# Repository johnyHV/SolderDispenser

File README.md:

# Solder paste dispenser

# Change Log

### Version 1.1 [HW v1.1, SW v1.1]
- pridana funkcia auto pull efektu. Toznamena, ze po pusteni PUSH tlacidla sa krokovy motor otoci o X krokov spat, vdaka comu prestane tlacit na spajkovaciu pastu. Efekt mozete zapnut pomocou definicie **M_A_PULL_E** v subore **MCU_cfg.h**.  Definiciou **M_A_PULL_ST** nastavujete pocet krokov o kolko sa krokov motor vrati spet. Tuto hodnotu je potrebne odladit pre kazdeho uzivatela, no myslim ze 100 krokov bude dost. Definiciou **M_A_PULL_SP** nastavite rychlost otacania krokoveho motora, pri otacani.
- pridany vypis SW verzie do konzoly
- aktualizovana doxygen dokumentacia

### Version 1.2 [HW v1.1, SW v1.2]
- pridana moznost zapnutia/vypnutia auto pull modu pomocou tlacidiel.  Defaultne je auto pull mod vypnuty, pomocou definicie **M_A_PULL_E**. Pre zapnutie je potrebne podrzat 5 sekund tlacidlo **MODE**. Po 5 sekundach zsvieti led **STATUS** na 1 sekundu. Vtedy je potrebne pustit tlacidlo **MODE**. Touto sekvenciou bol zapnuty auto pull mod. Ak ho chcete vypnut, znova je potrebne podrzat 5 sekund tlacidlo  **MODE**. Volba zapnutia/vypnutia auto pull modu sa neuklada do EEPROM pamete, cize po kazdom restarte je nastavena na hodnotu v definicii **M_A_PULL_E**.
- aktualizacia doxygen dokumentacie

### Version 1.3 [HW v1.2, SW v1.2]
- pridany kondenzator 1uF k napajaniu MCU

### Version 1.4 [HW v1.3, SW v1.2]
- pridany kondenzator 100nF k CH340 na 3,3V vystup.

# Bug

### Bug 0001
**Opis chyby:** 
chyba v HW zapojeni pre HW verzie 1.0, 1.1, 1.2. Chybajuci kondenzator 100nF pre CH340 na pine 4, proti zemi.

**Spravanie chyby:**
- OS moze mat problem pri detegcii zariadenia, v pripade pouzitia dlheho USB kabla. Pri dlzke kabla do 20cm bude zariadenie fungovat korektne.
- Moze vzniknut problem pri programovani MCU, kedy OS vypise hlasku nedetegovaneho USB zariadenia.
- Nahodne restarty MCU pocas pouzivania podavaca

**Riesenie:**
- potrebne prispajkovat kondenzator 100nF na pin 4 integrovaneho obvodu CH340 proti zemi. Tak ako je to zobrazene na fotografii

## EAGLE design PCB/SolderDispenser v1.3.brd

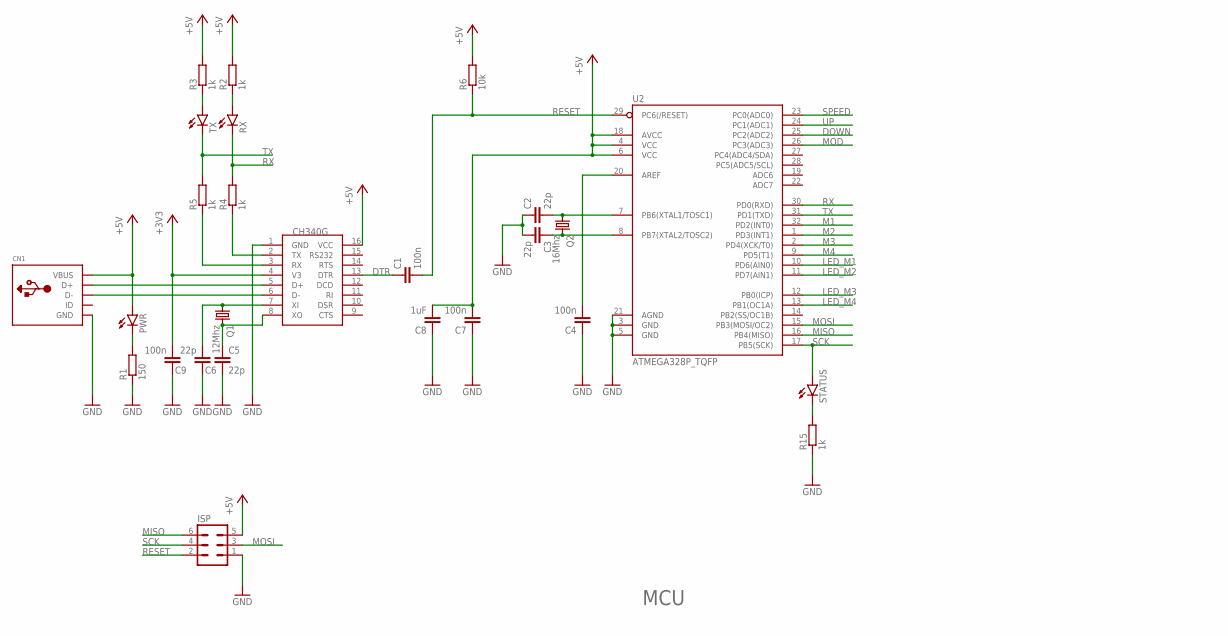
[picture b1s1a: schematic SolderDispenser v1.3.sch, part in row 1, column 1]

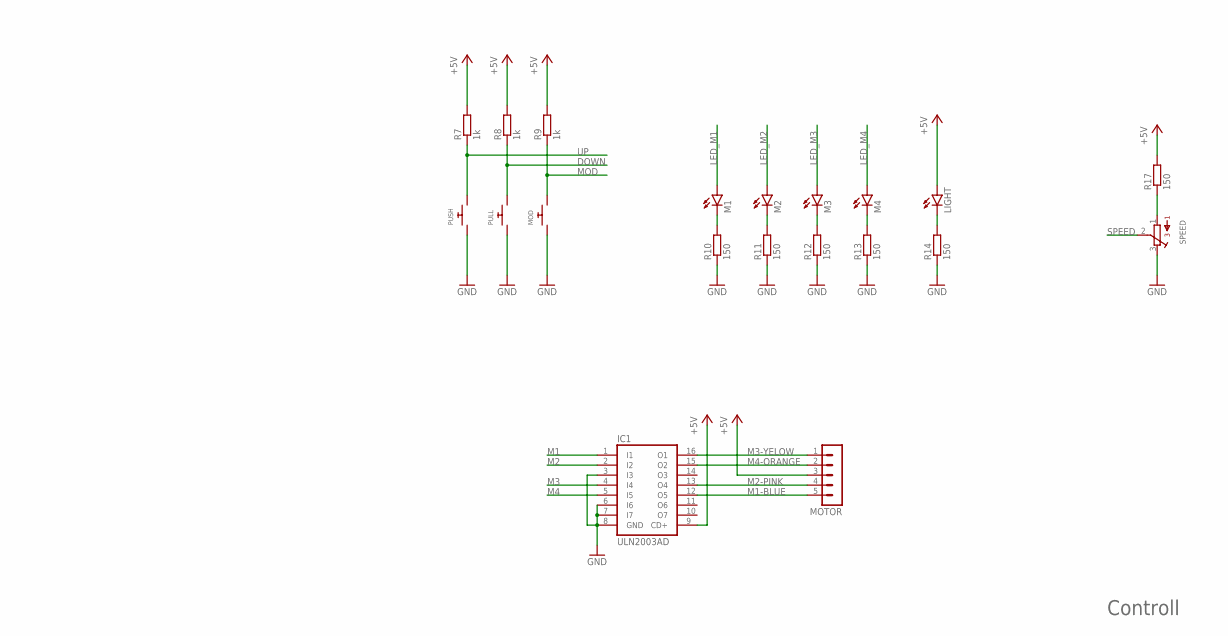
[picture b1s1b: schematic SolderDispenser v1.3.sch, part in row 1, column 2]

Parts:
C1, C4, C7, C9: 100n; C0805
C2, C3, C5, C6: 22p; C0805
C8: 1uF; C0805
CN1: USBMOLEX; USB-MINIB-THM-MOLEX
IC1: ULN2003AD; SO16
ISP: MA03-2
LIGHT: LED5MM
M1, M2, M3, M4: LEDSML0805; SML0805
MOD: SWITCH_PUSHBUTTONEVQ-PE; TACT_PANA-EVQ
MOTOR: MA05-1
PULL: SWITCH_PUSHBUTTONEVQ-PE; TACT_PANA-EVQ
PUSH: SWITCH_PUSHBUTTONEVQ-PE; TACT_PANA-EVQ
PWR: LEDSML0805; SML0805
Q1: 12Mhz; HC49UP
Q2: 16Mhz; HC49UP
R1, R10, R11, R12, R13, R14, R17: 150; R0805
R2, R3, R4, R5, R7, R8, R9, R15: 1k; R0805
R6: 10k; R0805
RX: LEDSML0805; SML0805
SPEED: 3362P
STATUS: LEDSML0805; SML0805
TX: LEDSML0805; SML0805
U2: ATMEGA328P_TQFP; TQFP32-08
U$1: CH340G; SOIC16

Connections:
+3V3: C9.2, U$1.4 (V3)
+5V: C7.2, C8.2, CN1.VBUS, IC1.9 (CD+), ISP.5, LIGHT.A, MOTOR.3, PWR.A, R2.2, R3.2, R6.2, R7.2, R8.2, R9.2, R17.2, U2.4 (VCC), U2.6 (VCC), U2.18 (AVCC), U$1.16 (VCC)
DOWN: PULL.P$2, R8.1, U2.25 (PC2(ADC2))
DTR: C1.1, U$1.13 (DTR)
GND: C2.1, C3.2, C4.1, C5.2, C6.1, C7.1, C8.1, C9.1, CN1.GND, IC1.3 (I3), IC1.6 (I6), IC1.7 (I7), IC1.8 (GND), ISP.1, MOD.P$1, PULL.P$1, PUSH.P$1, R1.1, R10.1, R11.1, R12.1, R13.1, R14.1, R15.1, SPEED.3, U2.3 (GND), U2.5 (GND), U2.21 (AGND), U$1.1 (GND)
LED_M1: M1.A, U2.10 (PD6(AIN0))
LED_M2: M2.A, U2.11 (PD7(AIN1))
LED_M3: M3.A, U2.12 (PB0(ICP))
LED_M4: M4.A, U2.13 (PB1(OC1A))
M1: IC1.1 (I1), U2.32 (PD2(INT0))
M1-BLUE: IC1.12 (O5), MOTOR.5
M2: IC1.2 (I2), U2.1 (PD3(INT1))
M2-PINK: IC1.13 (O4), MOTOR.4
M3: IC1.4 (I4), U2.2 (PD4(XCK/T0))
M3-YELOW: IC1.16 (O1), MOTOR.1
M4: IC1.5 (I5), U2.9 (PD5(T1))
M4-ORANGE: IC1.15 (O2), MOTOR.2
MISO: ISP.6, U2.16 (PB4(MISO))
MOD: MOD.P$2, R9.1, U2.26 (PC3(ADC3))
MOSI: ISP.3, U2.15 (PB3(MOSI/OC2))
unnamed: CN1.D+, U$1.5 (D+)
unnamed: PWR.C, R1.2
unnamed: CN1.D-, U$1.6 (D-)
unnamed: R5.1, U$1.3 (RX)
unnamed: R4.1, U$1.2 (TX)
unnamed: C2.2, Q2.1, U2.7 (PB6(XTAL1/TOSC1))
unnamed: C6.2, Q1.1, U$1.7 (XI)
unnamed: C5.1, Q1.2, U$1.8 (XO)
unnamed: R2.1, RX.A
unnamed: R3.1, TX.A
unnamed: C3.1, Q2.2, U2.8 (PB7(XTAL2/TOSC2))
unnamed: C4.2, U2.20 (AREF)
unnamed: M1.C, R10.2
unnamed: LIGHT.K (C), R14.2
unnamed: M2.C, R11.2
unnamed: R15.2, STATUS.C
unnamed: M3.C, R12.2
unnamed: M4.C, R13.2
unnamed: R17.1, SPEED.1
RESET: C1.2, ISP.2, R6.1, U2.29 (PC6(/RESET))
RX: R4.2, RX.C, U2.30 (PD0(RXD))
SCK: ISP.4, STATUS.A, U2.17 (PB5(SCK))
SPEED: SPEED.2, U2.23 (PC0(ADC0))
TX: R5.2, TX.C, U2.31 (PD1(TXD))
UP: PUSH.P$2, R7.1, U2.24 (PC1(ADC1))

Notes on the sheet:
MCU
Controll

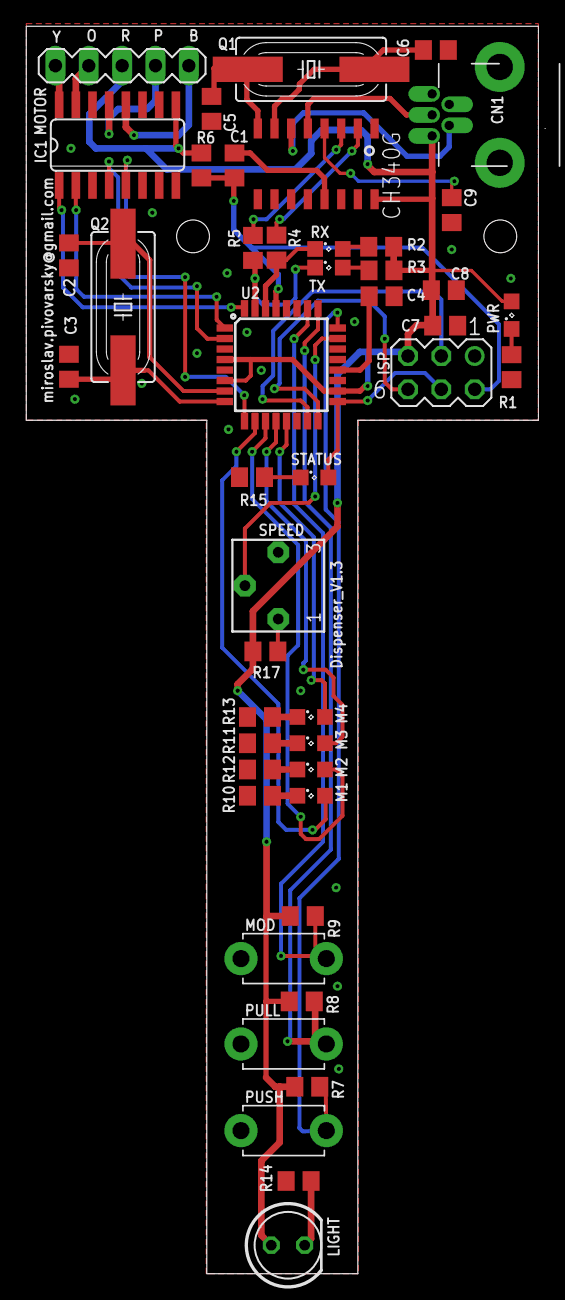
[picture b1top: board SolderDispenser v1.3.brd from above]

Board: 2 copper layers, 39.0 x 95.0 mm, 46 parts (0 on the bottom side), 45 nets.

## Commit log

2020-05-02 - Add source
2020-05-02 [3D]
    - Add 3D model for Syringe 18.6mm
2020-05-02 [Documentation]
    - Update documentation
2020-05-26 [Docu]
    - Add author
2020-10-30 [SW]
    - add auto pull effect
2020-10-30 [SW]
    - possibility to switch on the auto pull mode using the MODE button
2020-12-01 [HW]
    - add HW version 1.2
2020-12-18 fix HW bug for CH340 USB to UART converter
2020-12-18 add missing crystal value

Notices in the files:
parts and their libraries:
SparkFun-DigitalIC: Licensing: Creative Commons ShareAlike 4.0 International - https://creativecommons.org/licenses/by-sa/4.0
